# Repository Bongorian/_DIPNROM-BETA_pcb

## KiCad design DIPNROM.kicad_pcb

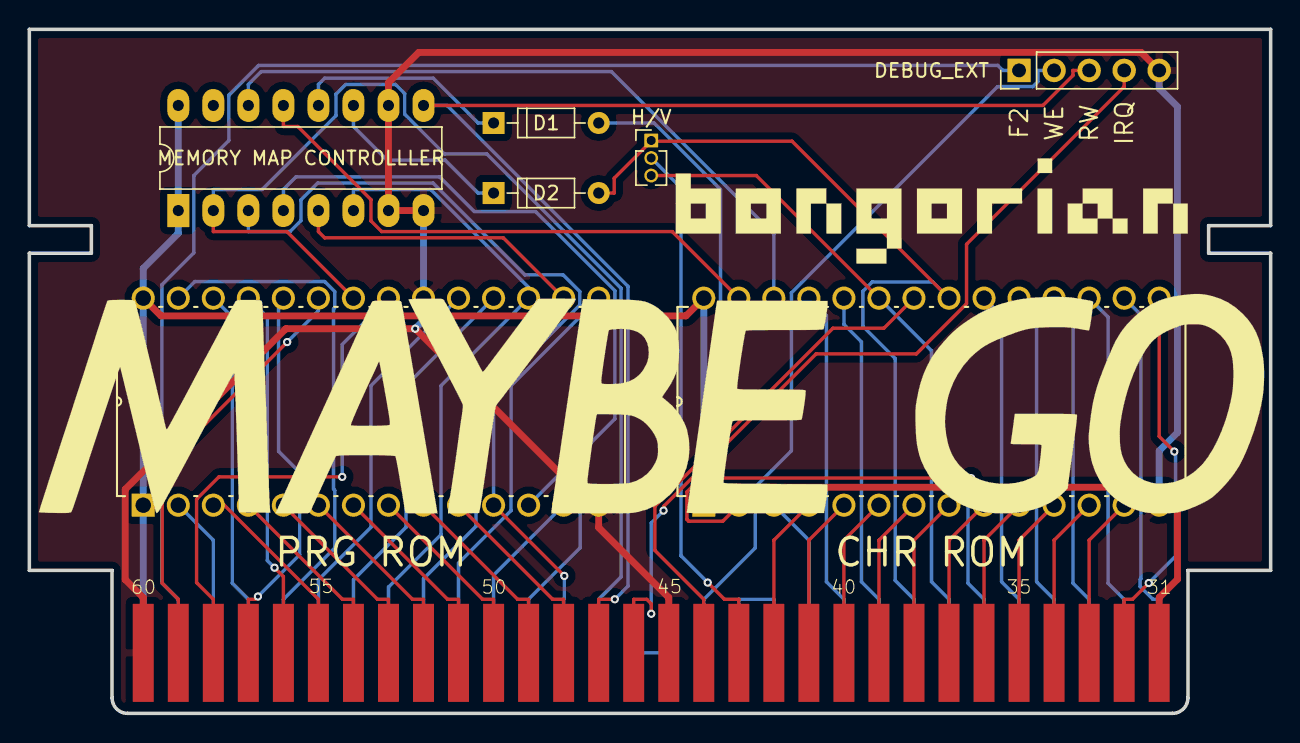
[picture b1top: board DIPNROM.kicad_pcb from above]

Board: 2 copper layers, 90.0 x 49.6 mm, 8 parts (0 on the bottom side), 60 nets.

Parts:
CHR ROM: M27C512-90B6; DIP254P1524X444-28
D1, D2: Jumper; D_DO-35_SOD27_P7.62mm_Horizontal
DEBUG_EXT: DEBUG; Pin_Header_Straight_1x05_Pitch2.54mm
H/V: Conn_01x03; Pin_Header_Straight_1x03_Pitch1.27mm
J2: EDGE CONNECTOR; FAMICOM
MEMORY MAP CONTROLLLER: 74LS161; DIP-16_W7.62mm_LongPads
PRG ROM: M27C512-90B6; DIP254P1524X444-28

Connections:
/PA13: J2.12, J2.13
A0: J2.48, PRG ROM.10
A1: J2.49, PRG ROM.9
A2: J2.50, PRG ROM.8
A3: J2.51, PRG ROM.7
A4: J2.52, PRG ROM.6
A5: J2.53, PRG ROM.5
A6: J2.54, PRG ROM.4
A7: J2.55, PRG ROM.3
A8: J2.56, PRG ROM.25
A9: J2.57, PRG ROM.24
A10: J2.58, PRG ROM.21
A11: J2.59, PRG ROM.23
A12: J2.28, PRG ROM.2
A13: J2.27, PRG ROM.26
A14: J2.26, PRG ROM.27
D0: J2.18, MEMORY MAP CONTROLLLER.3, PRG ROM.11
D1: J2.19, MEMORY MAP CONTROLLLER.4, PRG ROM.12
D2: J2.20, PRG ROM.13
D3: J2.21, PRG ROM.15
D4: J2.22, MEMORY MAP CONTROLLLER.5, PRG ROM.16
D5: J2.23, MEMORY MAP CONTROLLLER.6, PRG ROM.17
D6: J2.24, PRG ROM.18
D7: J2.25, PRG ROM.19
F2: DEBUG_EXT.1, J2.29
GND: CHR ROM.14, DEBUG_EXT.5, J2.45, J2.60, MEMORY MAP CONTROLLLER.7, MEMORY MAP CONTROLLLER.8, MEMORY MAP CONTROLLLER.10, PRG ROM.14, PRG ROM.20
IN: J2.15, J2.16
IRQ: DEBUG_EXT.4, J2.46
unnamed: CHR ROM.26, MEMORY MAP CONTROLLLER.14
unnamed: CHR ROM.27, MEMORY MAP CONTROLLLER.13
unnamed: D1.1, MEMORY MAP CONTROLLLER.12
unnamed: D2.1, MEMORY MAP CONTROLLLER.11
PA0: CHR ROM.10, J2.36
PA1: CHR ROM.9, J2.37
PA2: CHR ROM.8, J2.38
PA3: CHR ROM.7, J2.39
PA4: CHR ROM.6, J2.40
PA5: CHR ROM.5, J2.41
PA6: CHR ROM.4, J2.42
PA7: CHR ROM.3, J2.11
PA8: CHR ROM.25, J2.10
PA9: CHR ROM.24, J2.9
PA10: CHR ROM.21, D2.2, H/V.1, J2.8
PA11: CHR ROM.23, H/V.3, J2.7
PA12: CHR ROM.2, D1.2, J2.6
PA13: CHR ROM.20, J2.5
PD0: CHR ROM.11, J2.35
PD1: CHR ROM.12, J2.34
PD2: CHR ROM.13, J2.33
PD3: CHR ROM.15, J2.32
PD4: CHR ROM.16, J2.1
PD5: CHR ROM.17, J2.2
PD6: CHR ROM.18, J2.3
PD7: CHR ROM.19, J2.4
RD: CHR ROM.22, J2.44
ROMSEL: J2.17, MEMORY MAP CONTROLLLER.2, PRG ROM.22
RW: DEBUG_EXT.3, J2.47, MEMORY MAP CONTROLLLER.9
VCC: CHR ROM.1, CHR ROM.28, J2.30, J2.31, MEMORY MAP CONTROLLLER.1, MEMORY MAP CONTROLLLER.16, PRG ROM.1, PRG ROM.28
VRAMA10: H/V.2, J2.43
WE: DEBUG_EXT.2, J2.14

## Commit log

2018-06-16 init
